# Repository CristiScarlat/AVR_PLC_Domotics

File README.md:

This is a programmable PLC for home automations build around ATmega32, 
the electronic schematic can be found in the HW folder and the firmware in the AP_FW.
The firmware was writen in C using Atmel_Studio.
This PLC is programmable using an interface made in Java, the java project can be found in AP_SW directory

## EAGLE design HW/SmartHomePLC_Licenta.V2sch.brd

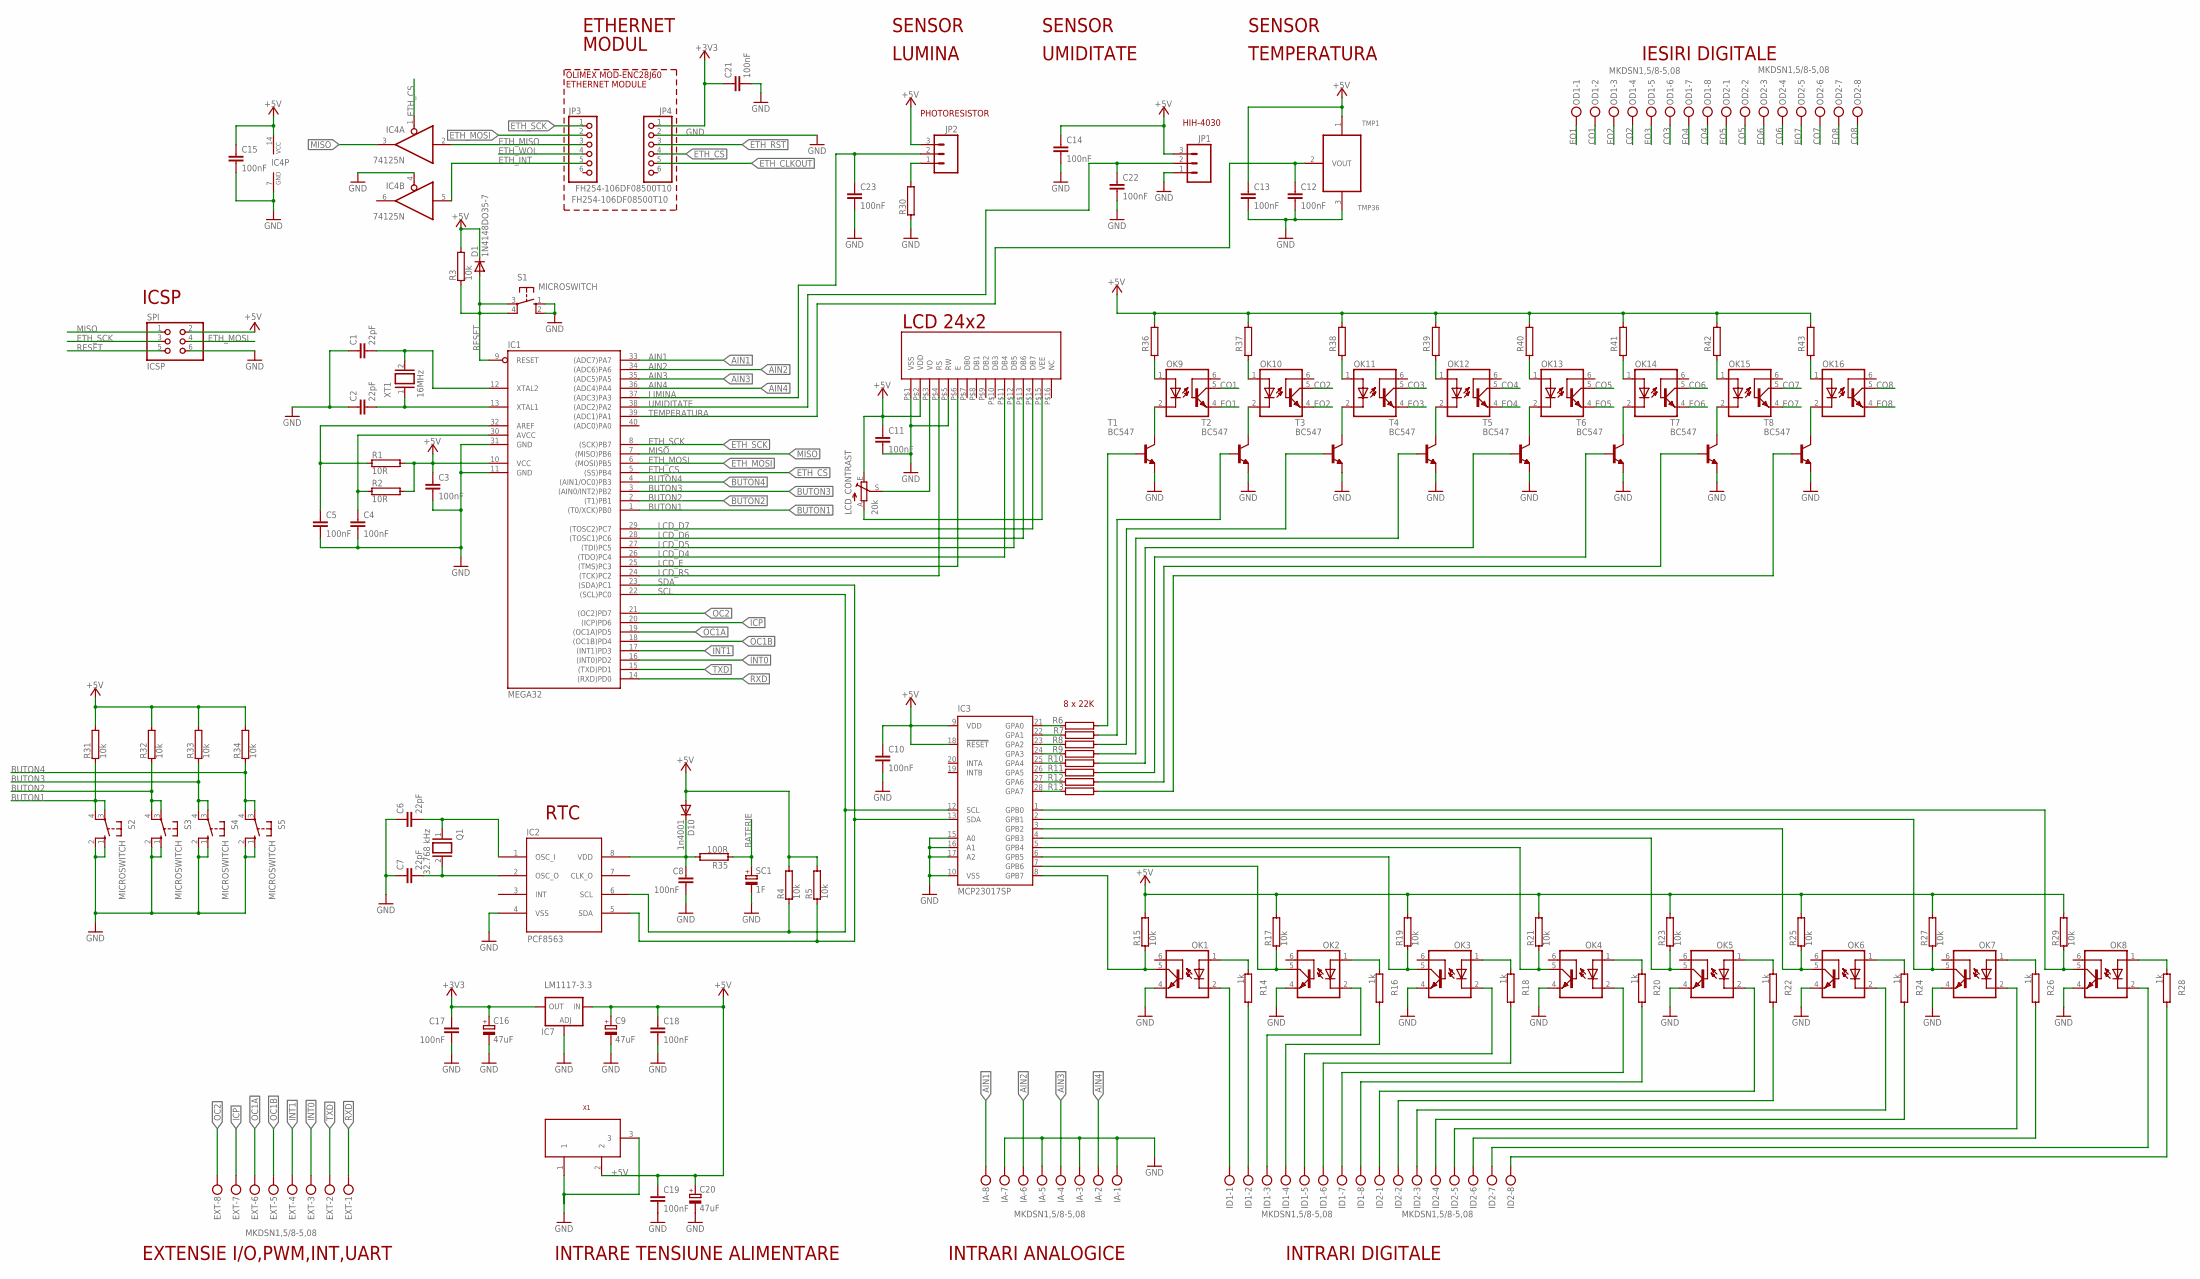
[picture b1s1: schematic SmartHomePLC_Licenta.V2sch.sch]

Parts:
C1, C2, C6, C7: 22pF; C2.5-2
C3, C4, C5, C8, C10, C11, C12, C13, C14, C15, C17, C18, C19, C21, C22, C23: 100nF; C5B2.5
C9, C16, C20: 47uF; E3,5-8
D1: 1N4148DO35-7; DO35-7
D10: 1n4001; DO35-10
EXT: MKDSN1,5/8-5,08
IA: MKDSN1,5/8-5,08
IC1: MEGA32; DIL40
IC2: PCF8563P; DIL08
IC3: MCP23017SP; DIL28-3
IC4: 74125N; DIL14
IC7: LM1117-3.3; 317TS
ID1, ID2: MKDSN1,5/8-5,08
JP1, JP2: M03LONGPADS; 1X03_LONGPADS
JP3, JP4: FH254-106DF08500T10; 1X06
LCD_CONTRAST: 20k; CA6V
OD1, OD2: MKDSN1,5/8-5,08
OK1, OK2, OK3, OK4, OK5, OK6, OK7, OK8, OK9, OK10, OK11, OK12, OK13, OK14, OK15, OK16: 4N35; DIL06
Q1: 32.768 kHz; QS
R1, R2: 10R; RS1/8
R3, R4, R5, R15, R17, R19, R21, R23, R25, R27, R29, R31, R32, R33, R34: 10k; RS1/8
R6, R7, R8, R9, R10, R11, R12, R13, R30, R36, R37, R38, R39, R40, R41, R42, R43: REZISTORSRS1/8; RS1/8
R14, R16, R18, R20, R22, R24, R26, R28: 1k; RS1/8
R35: 100R; RS1/8
S1, S2, S3, S4, S5: MICROSWITCH; B3F-10XX
SC1: 1F; DYNACAP-DB_1_3
SPI: ICSP; 2X03
T1, T2, T3, T4, T5, T6, T7, T8: BC547; BC-TO92
TMP1: TMP36; BC-TO92
U1: LCD_RC2402
X1: 0018_19746-POWER-SUPPLY; POWERSUPPLY_DC-21MM
XT1: 16MHz; QS

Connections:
+3V3: C16.+, C17.1, C21.1, IC7.2 (OUT), JP4.1
+5V: C3.1, C9.+, C10.1, C11.1, C13.1, C14.1, C15.1, C18.1, C19.1, C20.+, D1.C, D10.A, IC1.10 (VCC), IC3.9 (VDD), IC3.18 (!RESET), IC4.14 (VCC), IC7.3 (IN), JP1.3, JP2.3, LCD_CONTRAST.E, R1.2, R2.2, R3.2, R4.2, R5.2, R15.2, R17.2, R19.2, R21.2, R23.2, R25.2, R27.2, R29.2, R31.2, R32.2, R33.2, R34.2, R36.2, R37.2, R38.2, R39.2, R40.2, R41.2, R42.2, R43.2, SPI.2, TMP1.1 (+VS), U1.P$2 (VDD), X1.2
AIN1: IA.8, IC1.33 ((ADC7)PA7)
AIN2: IA.6, IC1.34 ((ADC6)PA6)
AIN3: IA.4, IC1.35 ((ADC5)PA5)
AIN4: IA.2, IC1.36 ((ADC4)PA4)
BATERIE: R35.1, SC1.+
BUTON1: IC1.1 ((T0/XCK)PB0), R31.1, S2.3, S2.4 (P1)
BUTON2: IC1.2 ((T1)PB1), R32.1, S3.3, S3.4 (P1)
BUTON3: IC1.3 ((AIN0/INT2)PB2), R33.1, S4.3, S4.4 (P1)
BUTON4: IC1.4 ((AIN1/OC0)PB3), R34.1, S5.3, S5.4 (P1)
CO1: OD1.2, OK9.5 (COL)
CO2: OD1.4, OK10.5 (COL)
CO3: OD1.6, OK11.5 (COL)
CO4: OD1.8, OK12.5 (COL)
CO5: OD2.2, OK13.5 (COL)
CO6: OD2.4, OK14.5 (COL)
CO7: OD2.6, OK15.5 (COL)
CO8: OD2.8, OK16.5 (COL)
EO1: OD1.1, OK9.4 (EMI)
EO2: OD1.3, OK10.4 (EMI)
EO3: OD1.5, OK11.4 (EMI)
EO4: OD1.7, OK12.4 (EMI)
EO5: OD2.1, OK13.4 (EMI)
EO6: OD2.3, OK14.4 (EMI)
EO7: OD2.5, OK15.4 (EMI)
EO8: OD2.7, OK16.4 (EMI)
ETH_CLKOUT: JP4.5
ETH_CS: IC1.5 ((SS)PB4), IC4.1 (OE), JP4.4
ETH_INT: IC4.5 (I), JP3.5
ETH_MISO: IC4.2 (I), JP3.3
ETH_MOSI: IC1.6 ((MOSI)PB5), JP3.2, SPI.4
ETH_RST: JP4.3
ETH_SCK: IC1.8 ((SCK)PB7), JP3.1, SPI.3
ETH_WOL: JP3.4
GND: C1.1, C2.1, C3.2, C4.2, C5.2, C6.1, C7.1, C8.2, C9.-, C10.2, C11.2, C12.2, C13.2, C14.2, C15.2, C16.-, C17.2, C18.2, C19.2, C20.-, C21.2, C22.2, C23.2, IA.1, IA.3, IA.5, IA.7, IC1.11 (GND), IC1.31 (GND), IC2.4 (VSS), IC3.10 (VSS), IC3.15 (A0), IC3.16 (A1), IC3.17 (A2), IC4.4 (OE), IC4.7 (GND), IC7.1 (ADJ), JP1.1, JP4.2, OK1.4 (EMI), OK2.4 (EMI), OK3.4 (EMI), OK4.4 (EMI), OK5.4 (EMI), OK6.4 (EMI), OK7.4 (EMI), OK8.4 (EMI), R30.1, S1.1 (S), S1.2 (S1), S2.1 (S), S2.2 (S1), S3.1 (S), S3.2 (S1), S4.1 (S), S4.2 (S1), S5.1 (S), S5.2 (S1), SC1.-, SPI.6, T1.1 (E), T2.1 (E), T3.1 (E), T4.1 (E), T5.1 (E), T6.1 (E), T7.1 (E), T8.1 (E), TMP1.3 (GND), U1.P$1 (VSS), U1.P$5 (RW), X1.1, X1.3
ICP: EXT.7, IC1.20 ((ICP)PD6)
INT0: EXT.3, IC1.16 ((INT0)PD2)
INT1: EXT.4, IC1.17 ((INT1)PD3)
LCD_D4: IC1.26 ((TDO)PC4), U1.P$11 (DB4)
LCD_D5: IC1.27 ((TDI)PC5), U1.P$12 (DB5)
LCD_D6: IC1.28 ((TOSC1)PC6), U1.P$13 (DB6)
LCD_D7: IC1.29 ((TOSC2)PC7), U1.P$14 (DB7)
LCD_E: IC1.25 ((TMS)PC3), U1.P$6 (E)
LCD_RS: IC1.24 ((TCK)PC2), U1.P$4 (RS)
LIMINA: C23.1, IC1.37 ((ADC3)PA3), JP2.2
MISO: IC1.7 ((MISO)PB6), IC4.3 (O), SPI.1
unnamed: C1.2, IC1.12 (XTAL2), XT1.2
unnamed: C2.2, IC1.13 (XTAL1), XT1.1
unnamed: C7.2, IC2.2 (OSC_O), Q1.2
unnamed: C4.1, IC1.30 (AVCC), R2.1
unnamed: C5.1, IC1.32 (AREF), R1.1
unnamed: IC3.28 (GPA7), R13.1
unnamed: IC3.27 (GPA6), R12.1
unnamed: IC3.26 (GPA5), R11.1
unnamed: IC3.25 (GPA4), R10.1
unnamed: IC3.24 (GPA3), R9.1
unnamed: C6.2, IC2.1 (OSC_I), Q1.1
unnamed: IC3.23 (GPA2), R8.1
unnamed: IC3.22 (GPA1), R7.1
unnamed: OK9.1 (A), R36.1
unnamed: IC3.21 (GPA0), R6.1
unnamed: OK9.2 (C), T1.3 (C)
unnamed: OK10.1 (A), R37.1
unnamed: R6.2, T1.2 (B)
unnamed: R7.2, T2.2 (B)
unnamed: OK11.1 (A), R38.1
unnamed: R8.2, T3.2 (B)
unnamed: R9.2, T4.2 (B)
unnamed: OK12.1 (A), R39.1
unnamed: OK13.1 (A), R40.1
unnamed: R10.2, T5.2 (B)
unnamed: LCD_CONTRAST.S, U1.P$3 (VO)
unnamed: LCD_CONTRAST.A, U1.P$15 (VEE)
unnamed: R11.2, T6.2 (B)
unnamed: OK14.1 (A), R41.1
unnamed: OK15.1 (A), R42.1
unnamed: R12.2, T7.2 (B)
unnamed: R13.2, T8.2 (B)
unnamed: OK1.1 (A), R14.1
unnamed: IC3.8 (GPB7), OK1.5 (COL), R15.1
unnamed: ID1.1, OK1.2 (C)
unnamed: OK16.1 (A), R43.1
unnamed: IC3.7 (GPB6), OK2.5 (COL), R17.1
unnamed: OK2.1 (A), R16.1
unnamed: ID1.3, OK2.2 (C)
unnamed: ID1.4, R16.2
unnamed: IC3.6 (GPB5), OK3.5 (COL), R19.1
unnamed: OK3.1 (A), R18.1
unnamed: ID1.5, OK3.2 (C)
unnamed: ID1.6, R18.2
unnamed: IC3.5 (GPB4), OK4.5 (COL), R21.1
unnamed: OK4.1 (A), R20.1
unnamed: ID1.7, OK4.2 (C)
unnamed: ID1.8, R20.2
unnamed: IC3.4 (GPB3), OK5.5 (COL), R23.1
unnamed: OK5.1 (A), R22.1
unnamed: ID2.1, OK5.2 (C)
unnamed: ID2.2, R22.2
unnamed: IC3.3 (GPB2), OK6.5 (COL), R25.1
unnamed: OK6.1 (A), R24.1
unnamed: ID2.3, OK6.2 (C)
unnamed: ID2.4, R24.2
unnamed: IC3.2 (GPB1), OK7.5 (COL), R27.1
unnamed: OK7.1 (A), R26.1
unnamed: OK10.2 (C), T2.3 (C)
unnamed: ID2.6, R26.2
unnamed: IC3.1 (GPB0), OK8.5 (COL), R29.1
unnamed: OK8.1 (A), R28.1
unnamed: ID2.7, OK8.2 (C)
unnamed: ID2.8, R28.2
unnamed: JP2.1, R30.2
unnamed: OK11.2 (C), T3.3 (C)
unnamed: OK12.2 (C), T4.3 (C)
unnamed: OK13.2 (C), T5.3 (C)
unnamed: OK14.2 (C), T6.3 (C)
unnamed: OK15.2 (C), T7.3 (C)
unnamed: OK16.2 (C), T8.3 (C)
unnamed: ID2.5, OK7.2 (C)
unnamed: C8.1, D10.C, IC2.8 (VDD), R35.2
unnamed: ID1.2, R14.2
OC1A: EXT.6, IC1.19 ((OC1A)PD5)
OC1B: EXT.5, IC1.18 ((OC1B)PD4)
OC2: EXT.8, IC1.21 ((OC2)PD7)
RESET: D1.A, IC1.9 (RESET), R3.1, S1.3, S1.4 (P1), SPI.5
RXD: EXT.1, IC1.14 ((RXD)PD0)
SCL: IC1.22 ((SCL)PC0), IC2.6 (SCL), IC3.12 (SCL), R4.1
SDA: IC1.23 ((SDA)PC1), IC2.5 (SDA), IC3.13 (SDA), R5.1
TEMPERATURA: C12.1, IC1.39 ((ADC1)PA1), TMP1.2 (VOUT)
TXD: EXT.2, IC1.15 ((TXD)PD1)
UMIDITATE: C22.1, IC1.38 ((ADC2)PA2), JP1.2

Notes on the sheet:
PHOTORESISTOR
OLIMEX MOD-ENC28J60
ETHERNET MODULE
INTRARI ANALOGICE
INTRARI DIGITALE
IESIRI DIGITALE
SENSOR
LUMINA
UMIDITATE
TEMPERATURA
ETHERNET
MODUL
RTC
ICSP
LCD 24x2
8 x 22K
INTRARE TENSIUNE ALIMENTARE
HIH-4030
EXTENSIE I/O,PWM,INT,UART

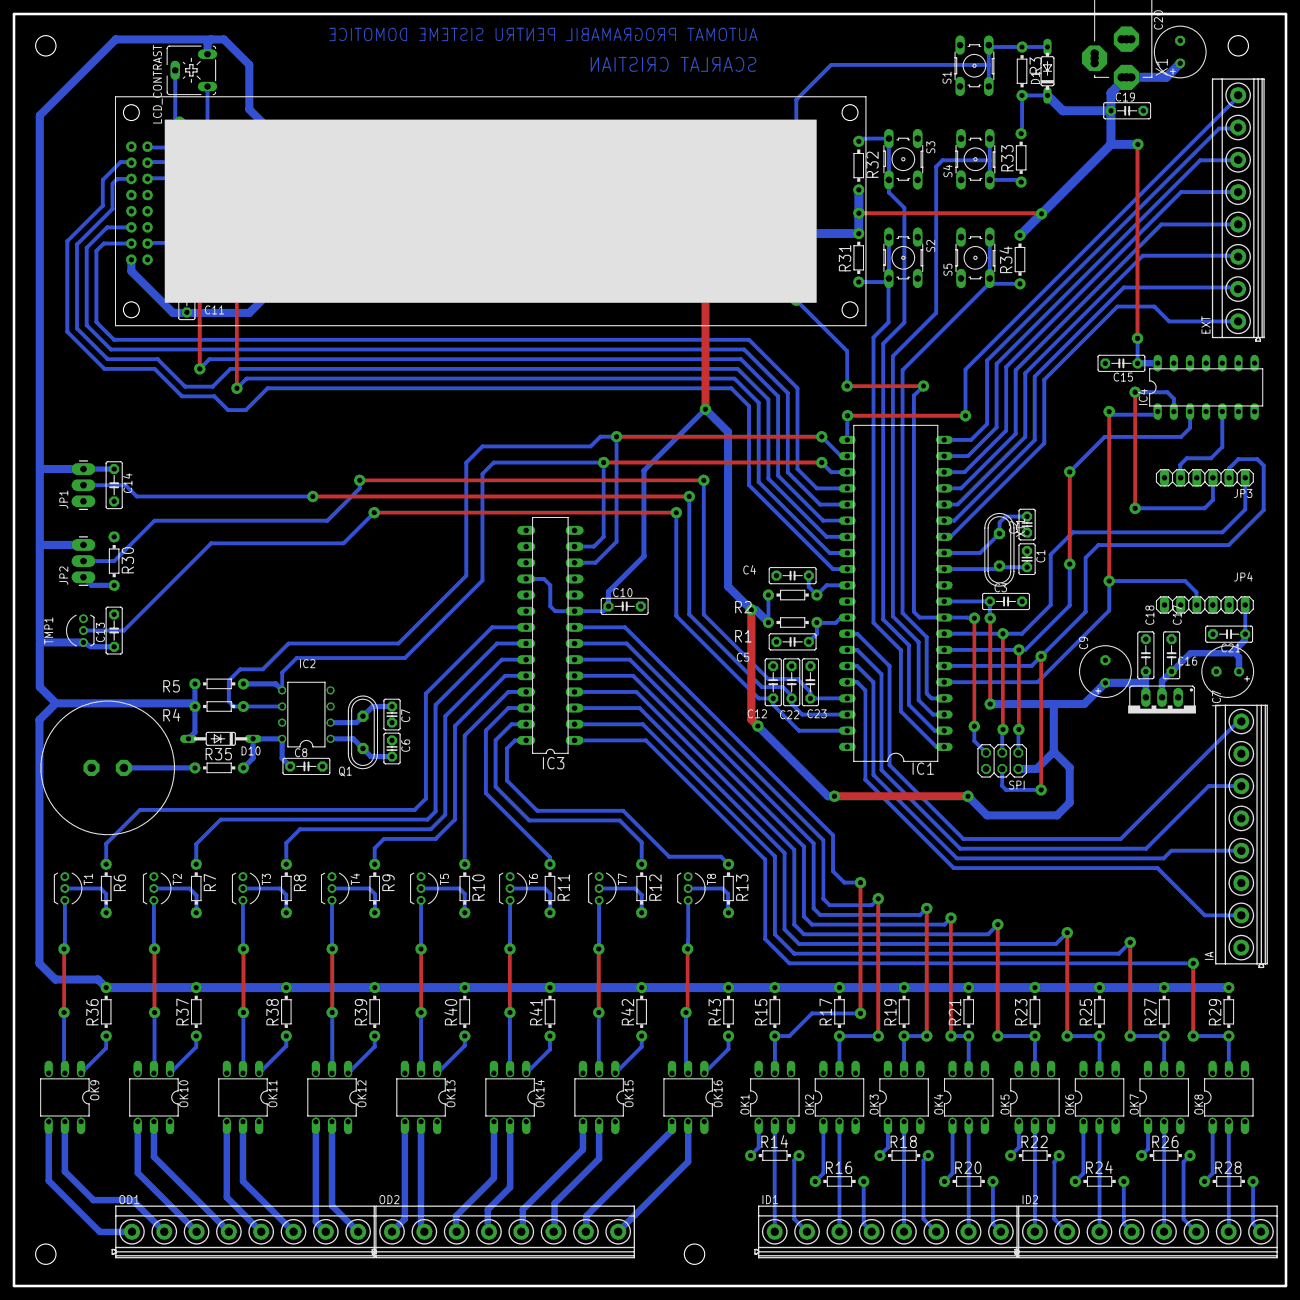
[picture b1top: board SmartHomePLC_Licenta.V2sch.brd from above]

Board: 2 copper layers, 200.0 x 200.0 mm, 120 parts (0 on the bottom side), 128 nets.

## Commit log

2018-01-20 first push
